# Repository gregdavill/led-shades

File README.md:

# ledShades

*Simple Arduino compatible RGB LED shades. Using an absurd quantinty of APA102 2020 smart LEDs.*

## 3d Render

When deciding between green and white PCBs I created this render. I ended up using white PCBs for my prototypes. Black would also look good.

---

## Schematic

Schematic is quite simple. The ATSAMD21 is loaded with the Arduino bootloader and programmed with FastLED to control the single array of 173 APA102 LEDs. Due to the voltage difference between the D21 and the APA102's I used two logic level converters for the clock and data lines.

---

## PCB

PCB was designed in KiCad and is a mostly single sided load. (Power connector, solders to back). The PCB is designed to act as the frame of the glasses directly. Some 3d printed arms are fitted to the edges of the glasses in older to attach them to your face.

---

## Firmware

The firmawre for the device is found in the fw folder. It is buil/t with the arduino IDE with 2 external libraries

* Adafruit GFX
* FastLED

The included code provides a simple wrapper to connect these libraries together to control the screen. Some small changes need to be made in orlder to accomadate good quality RGB data to the LEDs this includes changing the colour parameter in the GFX library to uint32_t type.

The main code supports 4 different modes of operation. Switching between modes is achieved by tapping the right side of the glasses. This triggers a tap event with the accelorometer.

## Development Timeline

* [x] Concept
* [x] Schematic
* [x] PCB Layout
* [x] 3d CAD export/cleanup
* [x] BOM export
* [x] Prototypes assembled
* [x] Firmware buildup
* [x] Additional Documentation
* [x] Small Volume Run

## License

MIT - See [LICENCE](LICENSE)

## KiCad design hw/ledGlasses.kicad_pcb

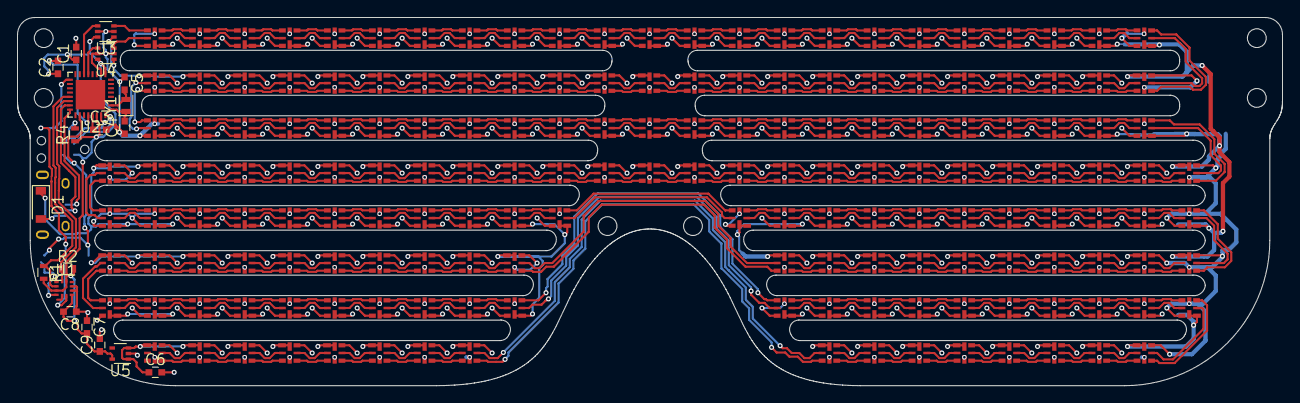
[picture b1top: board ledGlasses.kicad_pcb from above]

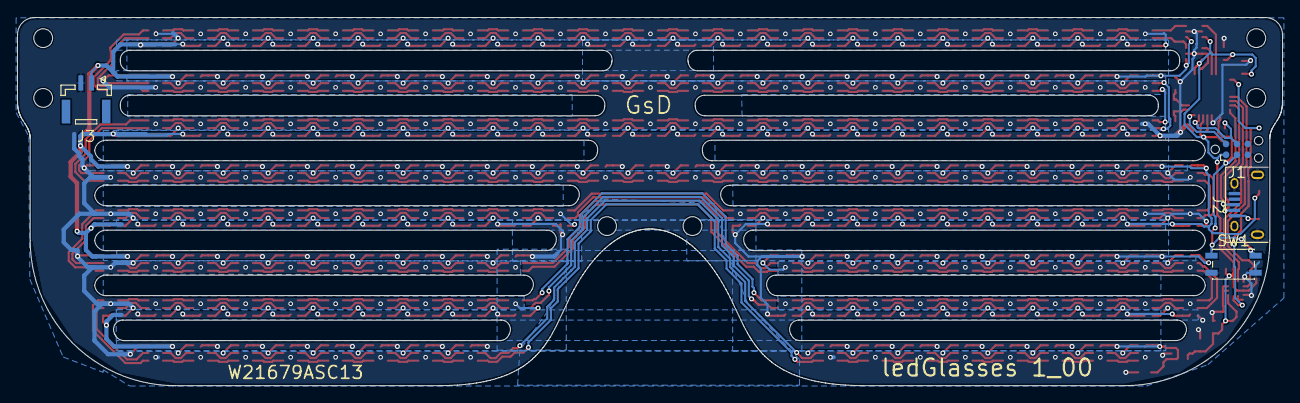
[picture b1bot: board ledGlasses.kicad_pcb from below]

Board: 2 copper layers, 148.1 x 43.1 mm, 201 parts (4 on the bottom side), 361 nets.

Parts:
C1, C2, C7, C8: 100nF; C_0603
C3, C6, C9: 1uF; C_0603
C4, C5: 16pF; C_0603
D1: Diode; D_SOD-123
J1: TC2030-CTX; Tag-Connect_TC2030-IDC-NL
J2: USB_OTG; USB_Micro-B
J3: PWR IN; JST_GH_BM02B-GHS-TBT_02x1.25mm_Straight
LED1, LED2, LED3, LED4, LED5, LED6, LED7, LED8, LED9, LED10, LED11, LED12, LED13, LED14, LED15, LED16, LED17, LED18, LED19, LED20, LED21, LED22, LED23, LED24, LED25, LED26, LED27, LED28, LED29, LED30, LED31, LED32, LED33, LED34, LED35, LED36, LED37, LED38, LED39, LED40, LED41, LED42, LED43, LED44, LED45, LED46, LED47, LED48, LED49, LED50, LED51, LED52, LED53, LED54, LED55, LED56, LED57, LED58, LED59, LED60, LED61, LED62, LED63, LED64, LED65, LED66, LED67, LED68, LED69, LED70, LED71, LED72, LED73, LED74, LED75, LED76, LED77, LED78, LED79, LED80, LED81, LED82, LED83, LED84, LED85, LED86, LED87, LED88, LED89, LED90, LED91, LED92, LED93, LED94, LED95, LED96, LED97, LED98, LED99, LED100, LED101, LED102, LED103, LED104, LED105, LED106, LED107, LED108, LED109, LED110, LED111, LED112, LED113, LED114, LED115, LED116, LED117, LED118, LED119, LED120, LED121, LED122, LED123, LED124, LED125, LED126, LED127, LED128, LED129, LED130, LED131, LED132, LED133, LED134, LED135, LED136, LED137, LED138, LED139, LED140, LED141, LED142, LED143, LED144, LED145, LED146, LED147, LED148, LED149, LED150, LED151, LED152, LED153, LED154, LED155, LED156, LED157, LED158, LED159, LED160, LED161, LED162, LED163, LED164, LED165, LED166, LED167, LED168, LED169, LED170, LED171, LED172: APA102; APA102_2020
MH1, MH2, MH3, MH4, MH5, MH6: MountingHole; MountingHole_2.2mm_M2_DIN965
R1, R2: 4K7; R_0603
R4: 1K; R_0603
SW1: TACT_SWITCH; SW_SPST_EVQP2
U1: BMA255
U2: SAMD20E17A-MU; QFN-32-1EP_5x5mm_Pitch0.5mm
U3, U4: SN74LVC1T45; SOT-363_SC-70-6
U5: MIC5365; SOT-353_SC-70-5
Y1: 32.768kHz; Crystal_SMD_2012-2pin_2.0x1.2mm

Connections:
+3V3: C1.1, C2.1, C7.2, C8.2, C9.1, J1.1, R1.2, R2.2, R4.1, U1.3, U1.7, U1.11, U2.9, U2.30, U3.6, U4.6, U5.5
+5V: C6.1, D1.1, J3.1, LED1.1, LED1.7, LED2.1, LED2.7, LED3.1, LED3.7, LED4.1, LED4.7, LED5.1, LED5.7, LED6.1, LED6.7, LED7.1, LED7.7, LED8.1, LED8.7, LED9.1, LED9.7, LED10.1, LED10.7, LED11.1, LED11.7, LED12.1, LED12.7, LED13.1, LED13.7, LED14.1, LED14.7, LED15.1, LED15.7, LED16.1, LED16.7, LED17.1, LED17.7, LED18.1, LED18.7, LED19.1, LED19.7, LED20.1, LED20.7, LED21.1, LED21.7, LED22.1, LED22.7, LED23.1, LED23.7, LED24.1, LED24.7, LED25.1, LED25.7, LED26.1, LED26.7, LED27.1, LED27.7, LED28.1, LED28.7, LED29.1, LED29.7, LED30.1, LED30.7, LED31.1, LED31.7, LED32.1, LED32.7, LED33.1, LED33.7, LED34.1, LED34.7, LED35.1, LED35.7, LED36.1, LED36.7, LED37.1, LED37.7, LED38.1, LED38.7, LED39.1, LED39.7, LED40.1, LED40.7, LED41.1, LED41.7, LED42.1, LED42.7, LED43.1, LED43.7, LED44.1, LED44.7, LED45.1, LED45.7, LED46.1, LED46.7, LED47.1, LED47.7, LED48.1, LED48.7, LED49.1, LED49.7, LED50.1, LED50.7, LED51.1, LED51.7, LED52.1, LED52.7, LED53.1, LED53.7, LED54.1, LED54.7, LED55.1, LED55.7, LED56.1, LED56.7, LED57.1, LED57.7, LED58.1, LED58.7, LED59.1, LED59.7, LED60.1, LED60.7, LED61.1, LED61.7, LED62.1, LED62.7, LED63.1, LED63.7, LED64.1, LED64.7, LED65.1, LED65.7, LED66.1, LED66.7, LED67.1, LED67.7, LED68.1, LED68.7, LED69.1, LED69.7, LED70.1, LED70.7, LED71.1, LED71.7, LED72.1, LED72.7, LED73.1, LED73.7, LED74.1, LED74.7, LED75.1, LED75.7, LED76.1, LED76.7, LED77.1, LED77.7, LED78.1, LED78.7, LED79.1, LED79.7, LED80.1, LED80.7, LED81.1, LED81.7, LED82.1, LED82.7, LED83.1, LED83.7, LED84.1, LED84.7, LED85.1, LED85.7, LED86.1, LED86.7, LED87.1, LED87.7, LED88.1, LED88.7, LED89.1, LED89.7, LED90.1, LED90.7, LED91.1, LED91.7, LED92.1, LED92.7, LED93.1, LED93.7, LED94.1, LED94.7, LED95.1, LED95.7, LED96.1, LED96.7, LED97.1, LED97.7, LED98.1, LED98.7, LED99.1, LED99.7, LED100.1, LED100.7, LED101.1, LED101.7, LED102.1, LED102.7, LED103.1, LED103.7, LED104.1, LED104.7, LED105.1, LED105.7, LED106.1, LED106.7, LED107.1, LED107.7, LED108.1, LED108.7, LED109.1, LED109.7, LED110.1, LED110.7, LED111.1, LED111.7, LED112.1, LED112.7, LED113.1, LED113.7, LED114.1, LED114.7, LED115.1, LED115.7, LED116.1, LED116.7, LED117.1, LED117.7, LED118.1, LED118.7, LED119.1, LED119.7, LED120.1, LED120.7, LED121.1, LED121.7, LED122.1, LED122.7, LED123.1, LED123.7, LED124.1, LED124.7, LED125.1, LED125.7, LED126.1, LED126.7, LED127.1, LED127.7, LED128.1, LED128.7, LED129.1, LED129.7, LED130.1, LED130.7, LED131.1, LED131.7, LED132.1, LED132.7, LED133.1, LED133.7, LED134.1, LED134.7, LED135.1, LED135.7, LED136.1, LED136.7, LED137.1, LED137.7, LED138.1, LED138.7, LED139.1, LED139.7, LED140.1, LED140.7, LED141.1, LED141.7, LED142.1, LED142.7, LED143.1, LED143.7, LED144.1, LED144.7, LED145.1, LED145.7, LED146.1, LED146.7, LED147.1, LED147.7, LED148.1, LED148.7, LED149.1, LED149.7, LED150.1, LED150.7, LED151.1, LED151.7, LED152.1, LED152.7, LED153.1, LED153.7, LED154.1, LED154.7, LED155.1, LED155.7, LED156.1, LED156.7, LED157.1, LED157.7, LED158.1, LED158.7, LED159.1, LED159.7, LED160.1, LED160.7, LED161.1, LED161.7, LED162.1, LED162.7, LED163.1, LED163.7, LED164.1, LED164.7, LED165.1, LED165.7, LED166.1, LED166.7, LED167.1, LED167.7, LED168.1, LED168.7, LED169.1, LED169.7, LED170.1, LED170.7, LED171.1, LED171.7, LED172.1, LED172.7, U3.1, U4.1, U5.1, U5.3
/clk20: LED20.2, LED21.5
/clk40: LED40.2, LED41.5
/clk60: LED60.2, LED61.5
/clk80: LED80.2, LED81.5
/clk104: LED104.2, LED105.5
/clk128: LED128.2, LED129.5
/clk152: LED152.2, LED153.5
/dat20: LED20.3, LED21.4
/dat40: LED40.3, LED41.4
/dat60: LED60.3, LED61.4
/dat80: LED80.3, LED81.4
/dat104: LED104.3, LED105.4
/dat128: LED128.3, LED129.4
/dat152: LED152.3, LED153.4
ACC_INT2: U1.6, U2.17
ACC_SCL: R2.1, U1.12, U2.22
ACC_SDA: R1.1, U1.2, U2.21
APA_CLK: U2.13, U4.4
APA_DAT: U2.14, U3.4
GND: C1.2, C2.2, C3.2, C4.1, C5.1, C6.2, C7.1, C8.1, C9.2, J1.5, J2.5, J2.6, J3.2, LED1.6, LED1.8, LED2.6, LED2.8, LED3.6, LED3.8, LED4.6, LED4.8, LED5.6, LED5.8, LED6.6, LED6.8, LED7.6, LED7.8, LED8.6, LED8.8, LED9.6, LED9.8, LED10.6, LED10.8, LED11.6, LED11.8, LED12.6, LED12.8, LED13.6, LED13.8, LED14.6, LED14.8, LED15.6, LED15.8, LED16.6, LED16.8, LED17.6, LED17.8, LED18.6, LED18.8, LED19.6, LED19.8, LED20.6, LED20.8, LED21.6, LED21.8, LED22.6, LED22.8, LED23.6, LED23.8, LED24.6, LED24.8, LED25.6, LED25.8, LED26.6, LED26.8, LED27.6, LED27.8, LED28.6, LED28.8, LED29.6, LED29.8, LED30.6, LED30.8, LED31.6, LED31.8, LED32.6, LED32.8, LED33.6, LED33.8, LED34.6, LED34.8, LED35.6, LED35.8, LED36.6, LED36.8, LED37.6, LED37.8, LED38.6, LED38.8, LED39.6, LED39.8, LED40.6, LED40.8, LED41.6, LED41.8, LED42.6, LED42.8, LED43.6, LED43.8, LED44.6, LED44.8, LED45.6, LED45.8, LED46.6, LED46.8, LED47.6, LED47.8, LED48.6, LED48.8, LED49.6, LED49.8, LED50.6, LED50.8, LED51.6, LED51.8, LED52.6, LED52.8, LED53.6, LED53.8, LED54.6, LED54.8, LED55.6, LED55.8, LED56.6, LED56.8, LED57.6, LED57.8, LED58.6, LED58.8, LED59.6, LED59.8, LED60.6, LED60.8, LED61.6, LED61.8, LED62.6, LED62.8, LED63.6, LED63.8, LED64.6, LED64.8, LED65.6, LED65.8, LED66.6, LED66.8, LED67.6, LED67.8, LED68.6, LED68.8, LED69.6, LED69.8, LED70.6, LED70.8, LED71.6, LED71.8, LED72.6, LED72.8, LED73.6, LED73.8, LED74.6, LED74.8, LED75.6, LED75.8, LED76.6, LED76.8, LED77.6, LED77.8, LED78.6, LED78.8, LED79.6, LED79.8, LED80.6, LED80.8, LED81.6, LED81.8, LED82.6, LED82.8, LED83.6, LED83.8, LED84.6, LED84.8, LED85.6, LED85.8, LED86.6, LED86.8, LED87.6, LED87.8, LED88.6, LED88.8, LED89.6, LED89.8, LED90.6, LED90.8, LED91.6, LED91.8, LED92.6, LED92.8, LED93.6, LED93.8, LED94.6, LED94.8, LED95.6, LED95.8, LED96.6, LED96.8, LED97.6, LED97.8, LED98.6, LED98.8, LED99.6, LED99.8, LED100.6, LED100.8, LED101.6, LED101.8, LED102.6, LED102.8, LED103.6, LED103.8, LED104.6, LED104.8, LED105.6, LED105.8, LED106.6, LED106.8, LED107.6, LED107.8, LED108.6, LED108.8, LED109.6, LED109.8, LED110.6, LED110.8, LED111.6, LED111.8, LED112.6, LED112.8, LED113.6, LED113.8, LED114.6, LED114.8, LED115.6, LED115.8, LED116.6, LED116.8, LED117.6, LED117.8, LED118.6, LED118.8, LED119.6, LED119.8, LED120.6, LED120.8, LED121.6, LED121.8, LED122.6, LED122.8, LED123.6, LED123.8, LED124.6, LED124.8, LED125.6, LED125.8, LED126.6, LED126.8, LED127.6, LED127.8, LED128.6, LED128.8, LED129.6, LED129.8, LED130.6, LED130.8, LED131.6, LED131.8, LED132.6, LED132.8, LED133.6, LED133.8, LED134.6, LED134.8, LED135.6, LED135.8, LED136.6, LED136.8, LED137.6, LED137.8, LED138.6, LED138.8, LED139.6, LED139.8, LED140.6, LED140.8, LED141.6, LED141.8, LED142.6, LED142.8, LED143.6, LED143.8, LED144.6, LED144.8, LED145.6, LED145.8, LED146.6, LED146.8, LED147.6, LED147.8, LED148.6, LED148.8, LED149.6, LED149.8, LED150.6, LED150.8, LED151.6, LED151.8, LED152.6, LED152.8, LED153.6, LED153.8, LED154.6, LED154.8, LED155.6, LED155.8, LED156.6, LED156.8, LED157.6, LED157.8, LED158.6, LED158.8, LED159.6, LED159.8, LED160.6, LED160.8, LED161.6, LED161.8, LED162.6, LED162.8, LED163.6, LED163.8, LED164.6, LED164.8, LED165.6, LED165.8, LED166.6, LED166.8, LED167.6, LED167.8, LED168.6, LED168.8, LED169.6, LED169.8, LED170.6, LED170.8, LED171.6, LED171.8, LED172.6, LED172.8, SW1.2, U1.1, U1.4, U1.8, U1.9, U2.10, U2.28, U3.2, U3.5, U4.2, U4.5, U5.2
unnamed: C3.1, U2.29
unnamed: C4.2, U2.1, Y1.1
unnamed: C5.2, U2.2, Y1.2
unnamed: D1.2, J2.1
unnamed: LED1.2, LED2.5
unnamed: LED1.3, LED2.4
unnamed: LED1.4, U3.3
unnamed: LED1.5, U4.3
unnamed: LED2.2, LED3.5
unnamed: LED2.3, LED3.4
unnamed: LED3.2, LED4.5
unnamed: LED3.3, LED4.4
unnamed: LED4.2, LED5.5
unnamed: LED4.3, LED5.4
unnamed: LED5.2, LED6.5
unnamed: LED5.3, LED6.4
unnamed: LED6.2, LED7.5
unnamed: LED6.3, LED7.4
unnamed: LED7.2, LED8.5
unnamed: LED7.3, LED8.4
unnamed: LED8.2, LED9.5
unnamed: LED8.3, LED9.4
unnamed: LED10.2, LED11.5
unnamed: LED10.3, LED11.4
unnamed: LED9.3, LED10.4
unnamed: LED9.2, LED10.5
unnamed: LED11.2, LED12.5
unnamed: LED11.3, LED12.4
unnamed: LED12.2, LED13.5
unnamed: LED12.3, LED13.4
unnamed: LED13.2, LED14.5
unnamed: LED13.3, LED14.4
unnamed: LED14.2, LED15.5
unnamed: LED14.3, LED15.4
unnamed: LED15.2, LED16.5
unnamed: LED15.3, LED16.4
unnamed: LED16.2, LED17.5
unnamed: LED16.3, LED17.4
unnamed: LED17.2, LED18.5
unnamed: LED17.3, LED18.4
unnamed: LED18.2, LED19.5
unnamed: LED18.3, LED19.4
unnamed: LED19.2, LED20.5
unnamed: LED19.3, LED20.4
unnamed: LED21.2, LED22.5
unnamed: LED21.3, LED22.4
unnamed: LED22.2, LED23.5
unnamed: LED22.3, LED23.4
unnamed: LED23.2, LED24.5
unnamed: LED23.3, LED24.4
unnamed: LED24.2, LED25.5
unnamed: LED24.3, LED25.4
unnamed: LED25.2, LED26.5
unnamed: LED25.3, LED26.4
unnamed: LED26.2, LED27.5
unnamed: LED26.3, LED27.4
unnamed: LED27.2, LED28.5
unnamed: LED27.3, LED28.4
unnamed: LED28.2, LED29.5
unnamed: LED28.3, LED29.4
unnamed: LED29.2, LED30.5
unnamed: LED29.3, LED30.4
unnamed: LED30.2, LED31.5
unnamed: LED30.3, LED31.4
unnamed: LED31.2, LED32.5
unnamed: LED31.3, LED32.4
unnamed: LED32.2, LED33.5
unnamed: LED32.3, LED33.4
unnamed: LED33.2, LED34.5
unnamed: LED33.3, LED34.4
unnamed: LED34.2, LED35.5
unnamed: LED34.3, LED35.4
unnamed: LED35.2, LED36.5
unnamed: LED35.3, LED36.4
unnamed: LED36.2, LED37.5
unnamed: LED36.3, LED37.4
unnamed: LED37.2, LED38.5
unnamed: LED37.3, LED38.4
unnamed: LED38.2, LED39.5
unnamed: LED38.3, LED39.4
unnamed: LED39.2, LED40.5
unnamed: LED39.3, LED40.4
unnamed: LED41.2, LED42.5
unnamed: LED41.3, LED42.4
unnamed: LED42.2, LED43.5
unnamed: LED42.3, LED43.4
unnamed: LED43.2, LED44.5
unnamed: LED43.3, LED44.4
unnamed: LED44.2, LED45.5
unnamed: LED44.3, LED45.4
unnamed: LED45.2, LED46.5
unnamed: LED45.3, LED46.4
unnamed: LED46.2, LED47.5
unnamed: LED46.3, LED47.4
unnamed: LED47.2, LED48.5
unnamed: LED47.3, LED48.4
unnamed: LED48.2, LED49.5
unnamed: LED48.3, LED49.4
unnamed: LED49.2, LED50.5
unnamed: LED49.3, LED50.4
unnamed: LED50.2, LED51.5
unnamed: LED50.3, LED51.4
unnamed: LED51.2, LED52.5
unnamed: LED51.3, LED52.4
unnamed: LED52.2, LED53.5
unnamed: LED52.3, LED53.4
unnamed: LED53.2, LED54.5
unnamed: LED53.3, LED54.4
unnamed: LED54.2, LED55.5
unnamed: LED54.3, LED55.4
unnamed: LED55.2, LED56.5
unnamed: LED55.3, LED56.4
unnamed: LED56.2, LED57.5
unnamed: LED56.3, LED57.4
unnamed: LED57.2, LED58.5
unnamed: LED57.3, LED58.4
unnamed: LED58.2, LED59.5
unnamed: LED58.3, LED59.4
unnamed: LED59.2, LED60.5
unnamed: LED59.3, LED60.4
unnamed: LED61.2, LED62.5
unnamed: LED61.3, LED62.4
unnamed: LED62.2, LED63.5
unnamed: LED62.3, LED63.4
unnamed: LED63.2, LED64.5
unnamed: LED63.3, LED64.4
unnamed: LED64.2, LED65.5
unnamed: LED64.3, LED65.4
unnamed: LED65.2, LED66.5
unnamed: LED65.3, LED66.4
unnamed: LED66.2, LED67.5
unnamed: LED66.3, LED67.4
unnamed: LED67.2, LED68.5
unnamed: LED67.3, LED68.4
unnamed: LED68.2, LED69.5
unnamed: LED68.3, LED69.4
unnamed: LED69.2, LED70.5
unnamed: LED69.3, LED70.4
unnamed: LED70.2, LED71.5
unnamed: LED70.3, LED71.4
unnamed: LED71.2, LED72.5
unnamed: LED71.3, LED72.4
unnamed: LED72.2, LED73.5
unnamed: LED72.3, LED73.4
unnamed: LED73.2, LED74.5
unnamed: LED73.3, LED74.4
unnamed: LED74.2, LED75.5
unnamed: LED74.3, LED75.4
unnamed: LED75.2, LED76.5
unnamed: LED75.3, LED76.4
unnamed: LED76.2, LED77.5
unnamed: LED76.3, LED77.4
unnamed: LED77.2, LED78.5
unnamed: LED77.3, LED78.4
unnamed: LED78.2, LED79.5
unnamed: LED78.3, LED79.4
unnamed: LED79.2, LED80.5
unnamed: LED79.3, LED80.4
unnamed: LED81.2, LED82.5
unnamed: LED81.3, LED82.4
unnamed: LED82.2, LED83.5
unnamed: LED82.3, LED83.4
unnamed: LED83.2, LED84.5
unnamed: LED83.3, LED84.4
unnamed: LED84.2, LED85.5
unnamed: LED84.3, LED85.4
unnamed: LED85.2, LED86.5
unnamed: LED85.3, LED86.4
unnamed: LED86.2, LED87.5
unnamed: LED86.3, LED87.4
unnamed: LED87.2, LED88.5
unnamed: LED87.3, LED88.4
unnamed: LED88.2, LED89.5
unnamed: LED88.3, LED89.4
unnamed: LED89.2, LED90.5
unnamed: LED89.3, LED90.4
unnamed: LED90.2, LED91.5
unnamed: LED90.3, LED91.4
unnamed: LED91.2, LED92.5
unnamed: LED91.3, LED92.4
unnamed: LED92.2, LED93.5
unnamed: LED92.3, LED93.4
unnamed: LED93.2, LED94.5
unnamed: LED93.3, LED94.4
unnamed: LED94.2, LED95.5
unnamed: LED94.3, LED95.4
unnamed: LED95.2, LED96.5
unnamed: LED95.3, LED96.4
unnamed: LED96.2, LED97.5
unnamed: LED96.3, LED97.4
unnamed: LED97.2, LED98.5
unnamed: LED97.3, LED98.4
unnamed: LED98.2, LED99.5
unnamed: LED98.3, LED99.4
unnamed: LED100.2, LED101.5
unnamed: LED100.3, LED101.4
unnamed: LED99.3, LED100.4
unnamed: LED99.2, LED100.5
unnamed: LED101.2, LED102.5
unnamed: LED101.3, LED102.4
unnamed: LED102.2, LED103.5
unnamed: LED102.3, LED103.4
unnamed: LED103.2, LED104.5
unnamed: LED103.3, LED104.4
unnamed: LED105.2, LED106.5
unnamed: LED105.3, LED106.4
unnamed: LED106.2, LED107.5
unnamed: LED106.3, LED107.4
unnamed: LED107.2, LED108.5
unnamed: LED107.3, LED108.4
unnamed: LED108.2, LED109.5
unnamed: LED108.3, LED109.4
unnamed: LED109.2, LED110.5
unnamed: LED109.3, LED110.4
unnamed: LED110.2, LED111.5
unnamed: LED110.3, LED111.4
unnamed: LED111.2, LED112.5
unnamed: LED111.3, LED112.4
unnamed: LED112.2, LED113.5
unnamed: LED112.3, LED113.4
unnamed: LED113.2, LED114.5
unnamed: LED113.3, LED114.4
unnamed: LED114.2, LED115.5
unnamed: LED114.3, LED115.4
unnamed: LED115.2, LED116.5
unnamed: LED115.3, LED116.4
unnamed: LED116.2, LED117.5
unnamed: LED116.3, LED117.4
unnamed: LED117.2, LED118.5
unnamed: LED117.3, LED118.4
unnamed: LED118.2, LED119.5
unnamed: LED118.3, LED119.4
unnamed: LED119.2, LED120.5
unnamed: LED119.3, LED120.4
unnamed: LED120.2, LED121.5
unnamed: LED120.3, LED121.4
unnamed: LED121.2, LED122.5
unnamed: LED121.3, LED122.4
unnamed: LED122.2, LED123.5
unnamed: LED122.3, LED123.4
unnamed: LED123.2, LED124.5
unnamed: LED123.3, LED124.4
unnamed: LED124.2, LED125.5
unnamed: LED124.3, LED125.4
unnamed: LED125.2, LED126.5
unnamed: LED125.3, LED126.4
unnamed: LED126.2, LED127.5
unnamed: LED126.3, LED127.4
unnamed: LED127.2, LED128.5
unnamed: LED127.3, LED128.4
unnamed: LED129.2, LED130.5
unnamed: LED129.3, LED130.4
unnamed: LED130.2, LED131.5
unnamed: LED130.3, LED131.4
unnamed: LED131.2, LED132.5
unnamed: LED131.3, LED132.4
unnamed: LED132.2, LED133.5
unnamed: LED132.3, LED133.4
unnamed: LED133.2, LED134.5
unnamed: LED133.3, LED134.4
unnamed: LED134.2, LED135.5
unnamed: LED134.3, LED135.4
unnamed: LED135.2, LED136.5
unnamed: LED135.3, LED136.4
unnamed: LED136.2, LED137.5
unnamed: LED136.3, LED137.4
unnamed: LED137.2, LED138.5
unnamed: LED137.3, LED138.4
unnamed: LED138.2, LED139.5
unnamed: LED138.3, LED139.4
unnamed: LED139.2, LED140.5
unnamed: LED139.3, LED140.4
unnamed: LED140.2, LED141.5
unnamed: LED140.3, LED141.4
unnamed: LED141.2, LED142.5
unnamed: LED141.3, LED142.4
unnamed: LED142.2, LED143.5
unnamed: LED142.3, LED143.4
unnamed: LED143.2, LED144.5
unnamed: LED143.3, LED144.4
unnamed: LED144.2, LED145.5
unnamed: LED144.3, LED145.4
unnamed: LED145.2, LED146.5
unnamed: LED145.3, LED146.4
unnamed: LED146.2, LED147.5
unnamed: LED146.3, LED147.4
unnamed: LED147.2, LED148.5
unnamed: LED147.3, LED148.4
unnamed: LED148.2, LED149.5
unnamed: LED148.3, LED149.4
unnamed: LED149.2, LED150.5
unnamed: LED149.3, LED150.4
unnamed: LED150.2, LED151.5
unnamed: LED150.3, LED151.4
unnamed: LED151.2, LED152.5
unnamed: LED151.3, LED152.4
unnamed: LED153.2, LED154.5
unnamed: LED153.3, LED154.4
unnamed: LED154.2, LED155.5
unnamed: LED154.3, LED155.4
unnamed: LED155.2, LED156.5
unnamed: LED155.3, LED156.4
unnamed: LED156.2, LED157.5
unnamed: LED156.3, LED157.4
unnamed: LED157.2, LED158.5
unnamed: LED157.3, LED158.4
unnamed: LED158.2, LED159.5
unnamed: LED158.3, LED159.4
unnamed: LED159.2, LED160.5
unnamed: LED159.3, LED160.4
unnamed: LED160.2, LED161.5
unnamed: LED160.3, LED161.4
unnamed: LED161.2, LED162.5
unnamed: LED161.3, LED162.4
unnamed: LED162.2, LED163.5
unnamed: LED162.3, LED163.4
unnamed: LED163.2, LED164.5
unnamed: LED163.3, LED164.4
unnamed: LED164.2, LED165.5
unnamed: LED164.3, LED165.4
unnamed: LED165.2, LED166.5
unnamed: LED165.3, LED166.4
unnamed: LED166.2, LED167.5
unnamed: LED166.3, LED167.4
unnamed: LED167.2, LED168.5
unnamed: LED167.3, LED168.4
unnamed: LED168.2, LED169.5
unnamed: LED168.3, LED169.4
unnamed: LED169.2, LED170.5
unnamed: LED169.3, LED170.4
unnamed: LED170.2, LED171.5
unnamed: LED170.3, LED171.4
unnamed: LED171.2, LED172.5
unnamed: LED171.3, LED172.4
RESET: J1.3, SW1.1, U2.26
SWCLK: J1.4, R4.2, U2.31
SWDIO: J1.2, U2.32
USB_D+: J2.3, U2.24
USB_D-: J2.2, U2.23

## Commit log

2017-11-26 Added PCB files.
2017-11-27 Cleanup, updates to README
2018-03-07 Added inital fw for project.
